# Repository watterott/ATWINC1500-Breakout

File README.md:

# ATWINC1500-Breakout
ATWINC1500-Breakout with Microchip WINC1500 WiFi Network Controller SoC and Microchip ATECC508A Crypto Authentication.

* [Microchip ATWINC1500B](http://www.microchip.com/wwwproducts/en/ATWINC1500) WiFi Network Controller (SPI)
* [Microchip ATECC508A](http://www.microchip.com/wwwproducts/en/ATECC508A) Crypto Authentication (I2C)
* Integrated WiFi and IPv4 stack
* 3.3V - 5V tolerant IOs
* Open-Source and released under the [Creative Commons Attribution Share-Alike License](https://creativecommons.org/licenses/by-sa/4.0/).
* **[Documentation on learn.watterott.com](https://learn.watterott.com)**

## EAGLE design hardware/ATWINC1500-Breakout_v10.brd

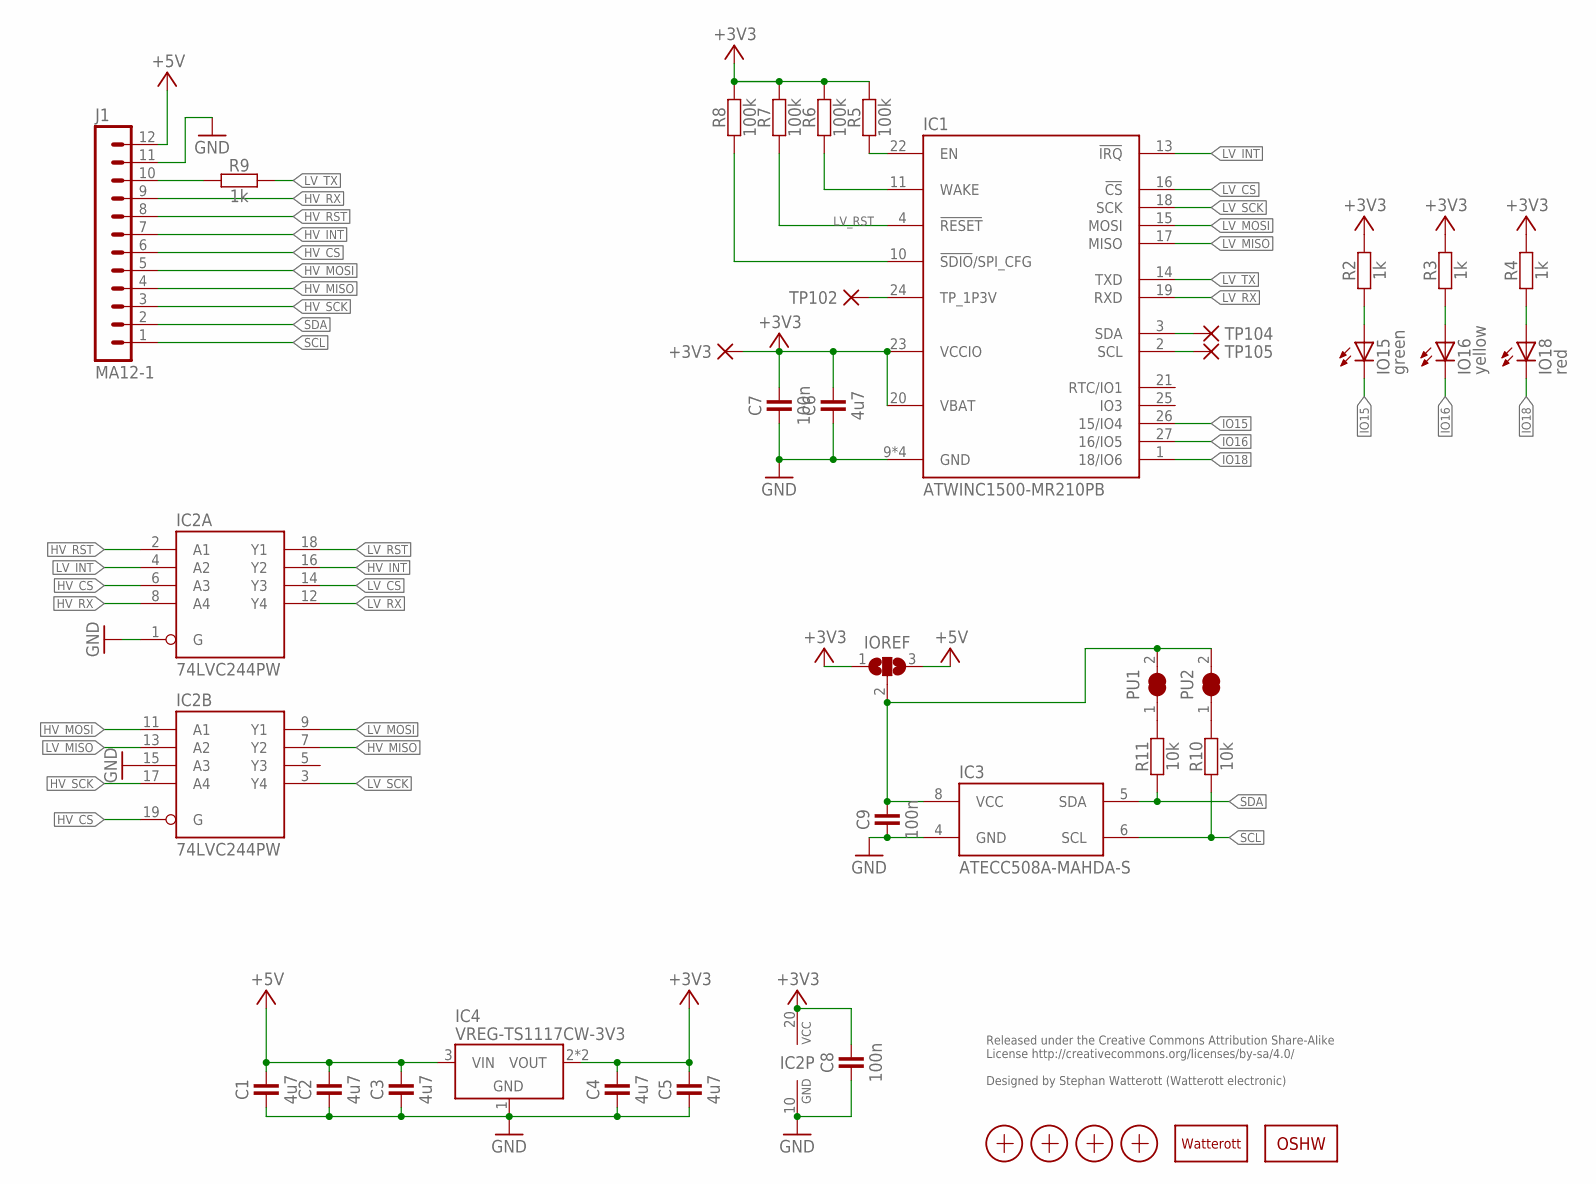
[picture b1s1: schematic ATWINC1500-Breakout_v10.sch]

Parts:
+3V3: PAD-1.27X1.27_NC
C1, C2, C3, C4, C5, C6: 4u7; C0603
C7: 100n; C0603
C8, C9: 100n; C0402
IC1: ATWINC1500-MR210PB; ATWINC1500-MX210
IC2: 74LVC244PW; TSSOP20
IC3: ATECC508A-MAHDA-S; UDFN8
IC4: VREG-TS1117CW-3V3; SOT223
IO15: green; C0603
IO16: yellow; C0603
IO18: red; C0603
IOREF: JUMPER3-0603-NC; JUMPER3-0603_NC
J1: MA12-1
LOGO1: LOGO-S_PLACE_M; SPARK_TPLACE_M
LOGO2: OSHW_LOGOX0100; OSHW_6X100
PU1, PU2: JUMPER2-0603-NC; JUMPER2-0603_NC
R2, R3, R4, R9: 1k; C0402
R5, R6, R7, R8: 100k; C0402
R10, R11: 10k; C0402
TP102, TP104, TP105: PAD-1.27X1.27_NC
X1, X2, X3, X4: PASSER-07; PASSER_07MM

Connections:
+3V3: +3V3.1, C4.2, C5.2, C6.2, C7.2, C8.2, IC1.20 (VBAT), IC1.23 (VCCIO), IC2.20 (VCC), IC4.2 (VOUT), IC4.4 (VOUT), IOREF.1, R2.2, R3.2, R4.2, R5.2, R6.2, R7.2, R8.2
+5V: C1.2, C2.2, C3.2, IC4.3 (VIN), IOREF.3, J1.12
GND: C1.1, C2.1, C3.1, C4.1, C5.1, C6.1, C7.1, C8.1, C9.1, IC1.9 (GND), IC1.12 (GND), IC1.28 (GND), IC1.GND, IC2.1 (G), IC2.10 (GND), IC2.15 (A3), IC3.4 (GND), IC4.1 (GND), J1.11
HV_CS: IC2.6 (A3), IC2.19 (G), J1.6
HV_INT: IC2.16 (Y2), J1.7
HV_MISO: IC2.7 (Y2), J1.4
HV_MOSI: IC2.11 (A1), J1.5
HV_RST: IC2.2 (A1), J1.8
HV_RX: IC2.8 (A4), J1.9
HV_SCK: IC2.17 (A4), J1.3
IO15: IC1.26 (15/IO4), IO15.C
IO16: IC1.27 (16/IO5), IO16.C
IO18: IC1.1 (18/IO6), IO18.C
IOREF: C9.2, IC3.8 (VCC), IOREF.2, PU1.2, PU2.2
LED15: IO15.A, R2.1
LED16: IO16.A, R3.1
LED18: IO18.A, R4.1
LV_CS: IC1.16 (!CS), IC2.14 (Y3)
LV_EN: IC1.22 (EN), R5.1
LV_INT: IC1.13 (!IRQ), IC2.4 (A2)
LV_MISO: IC1.17 (MISO), IC2.13 (A2)
LV_MOSI: IC1.15 (MOSI), IC2.9 (Y1)
LV_RST: IC1.4 (!RESET), IC2.18 (Y1), R7.1
LV_RX: IC1.19 (RXD), IC2.12 (Y4)
LV_SCK: IC1.18 (SCK), IC2.3 (Y4)
LV_TX: IC1.14 (TXD), R9.2
LV_WAKE: IC1.11 (WAKE), R6.1
unnamed: J1.10, R9.1
unnamed: PU2.1, R10.2
unnamed: PU1.1, R11.2
SCL: IC3.6 (SCL), J1.1, R10.1
SDA: IC3.5 (SDA), J1.2, R11.1
SPI_CFG: IC1.10 (!SDIO!/SPI_CFG), R8.1
TP: IC1.24 (TP_1P3V), TP102.1
WIFI_SCL: IC1.2 (SCL), TP105.1
WIFI_SDA: IC1.3 (SDA), TP104.1

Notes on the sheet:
Released under the Creative Commons Attribution Share-Alike License http://creativecommons.org/licenses/by-sa/4.0/ Designed by Stephan Watterott (Watterott electronic)

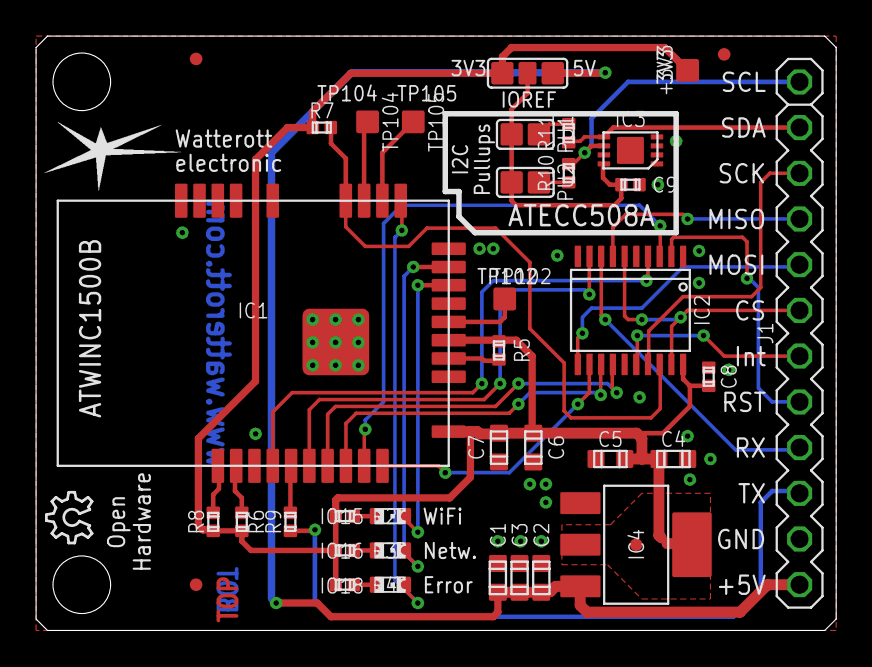
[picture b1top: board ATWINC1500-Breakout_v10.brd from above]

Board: 2 copper layers, 44.5 x 33.0 mm, 40 parts (0 on the bottom side), 36 nets.
